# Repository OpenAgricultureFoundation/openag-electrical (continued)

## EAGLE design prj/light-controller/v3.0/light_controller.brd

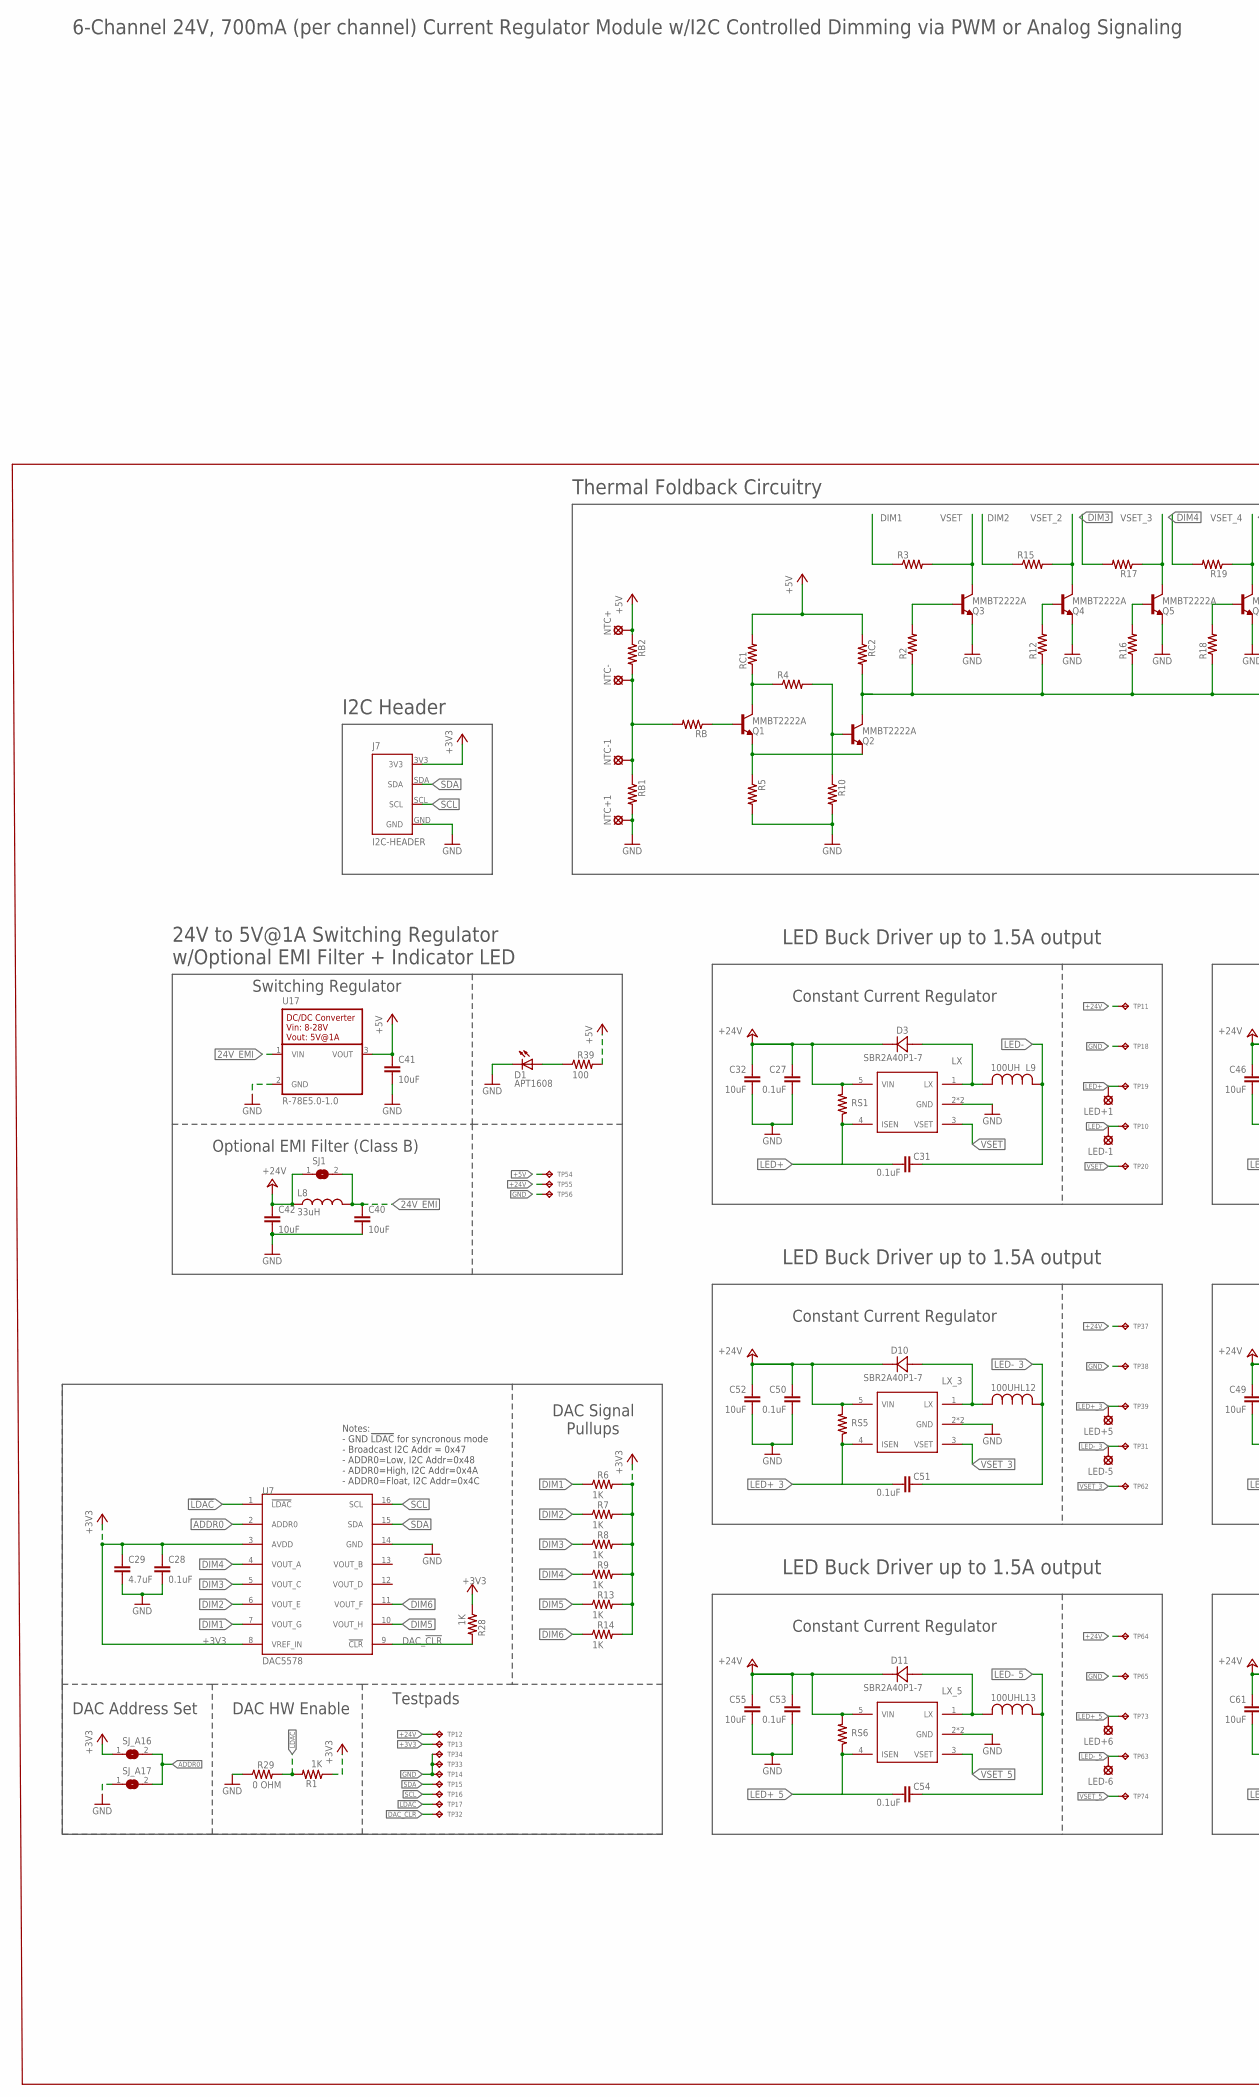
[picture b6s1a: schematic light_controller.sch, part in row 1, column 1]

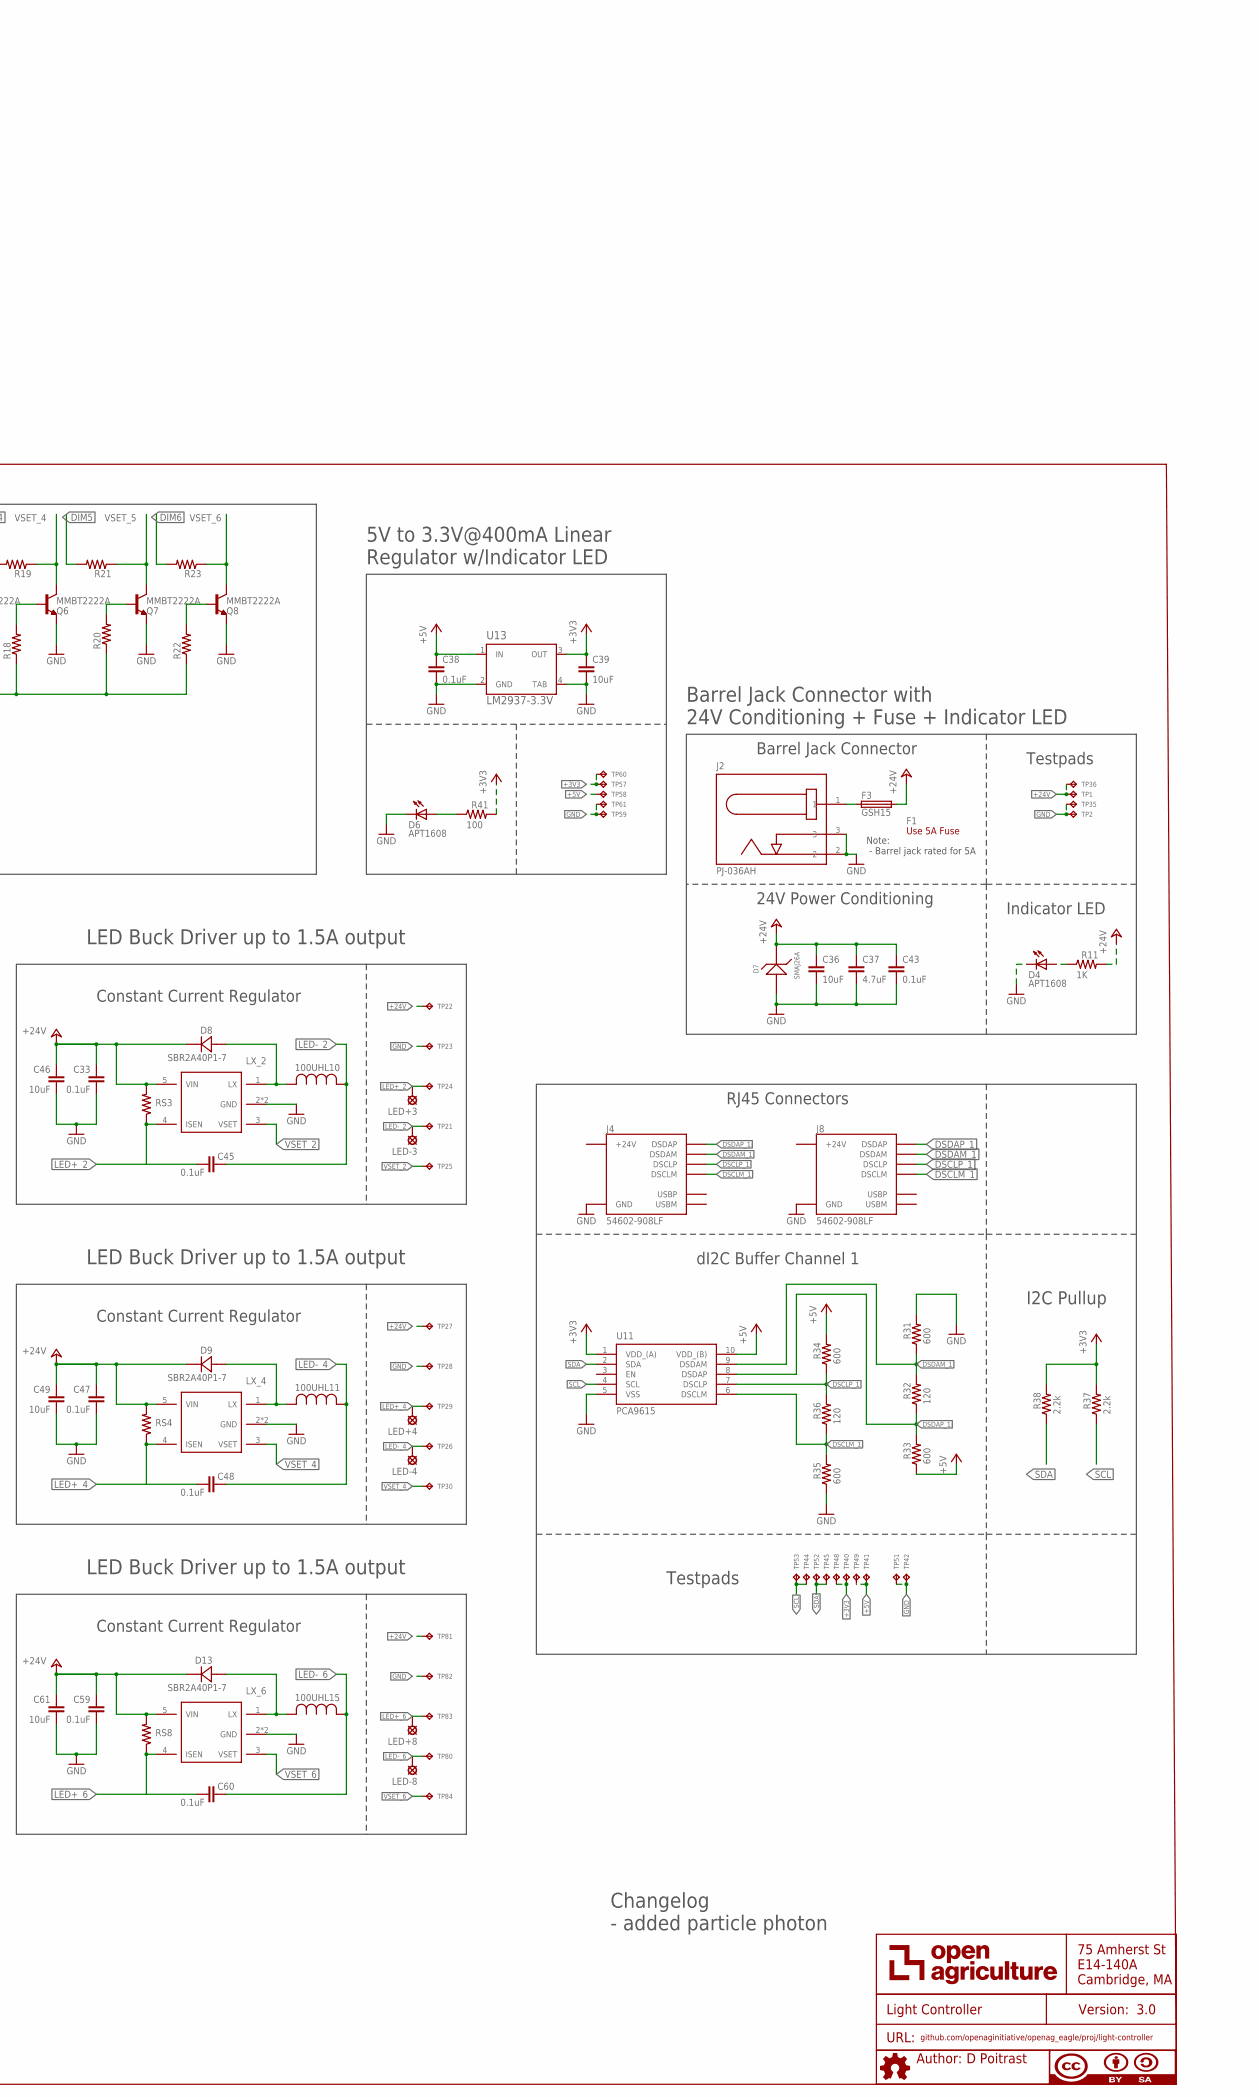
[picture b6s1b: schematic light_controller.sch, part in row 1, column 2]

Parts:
C27, C28, C31, C33, C38, C43, C45, C47, C48, C50, C51, C53, C54, C59, C60: 0.1uF; C0603
C29, C37: 4.7uF; C0805
C32, C36, C39, C40, C41, C42, C46, C49, C52, C55, C61: 10uF; C0805
D1, D4, D6: APT1608; CHIPLED_0603
D3, D8, D9, D10, D11, D13: SBR2A40P1-7; POWERDI123
D7: SMAJ26A; SMA
F1: Use 5A Fuse; FUSE-CARTRIDGE
F3: GSH15
J2: PJ-036AH; BARREL-JACK-PJ-036AH
J4, J8: 54602-908LF; RJ45-DI2C-USB-54602-908LF
J7: I2C-HEADER; HEADER-I2C
L8: 33uH; 29333C
L9, L10, L11, L12, L13, L15: 100UH; IND_BOURNS_SDR1307
LED+1, LED+3, LED+4, LED+5, LED+6, LED+8: SE14
LED-1, LED-3, LED-4, LED-5, LED-6, LED-8: SE14
NTC+, NTC+1: SE14
NTC-, NTC-1: SE14
Q1, Q2, Q3, Q4, Q5, Q6, Q7, Q8: MMBT2222A; SOT23-BEC
R1, R6, R7, R8, R9, R11, R13, R14, R28: 1K; RC0603N
R2, R3, R4, R5, R10, R12, R15, R16, R17, R18, R19, R20, R21, R22, R23: R-US_R0805W; R0805W
R29: 0 OHM; RC0603N
R31, R33, R34, R35: 600; RC0603N
R32, R36: 120; RC0603N
R37, R38: 2.2k; RC0603N
R39, R41: 100; RC0603N
RB, RB1, RB2: R-US_R0805W; R0805W
RC1, RC2: R-US_R0805W; R0805W
RS1, RS3, RS4, RS5, RS6, RS8: 6.34 ohm; R0805
SJ1: EMI-BYPASS
SJ_A16, SJ_A17: SOLDERJUMPERREFLOW_NOPASTE; SJ1
TP1, TP2, TP12, TP13, TP14, TP15, TP16, TP17, TP32, TP33, TP34, TP35, TP36, TP40, TP41, TP42, TP44, TP45, TP48, TP49, TP51, TP52, TP53, TP57, TP58, TP59, TP60, TP61: TPTP04R; TP04R
TP10, TP11, TP18, TP19, TP20, TP21, TP22, TP23, TP24, TP25, TP26, TP27, TP28, TP29, TP30, TP31, TP37, TP38, TP39, TP54, TP55, TP56, TP62, TP63, TP64, TP65, TP73, TP74, TP80, TP81, TP82, TP83, TP84: TPTP06R; TP06R
U7: DAC5578; TSSOP16
U11: PCA9615; SOP50P490X110-10N
U13: LM2937-3.3V; MP04A
U17: R-78E5.0-1.0
U$6: AUTHOR
U$7: TITLE
U$11, U$12, U$13, U$14, U$15, U$17: AL8861

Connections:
24V_EMI: C40.1, L8.2, SJ1.2, U17.1 (VIN)
24V_IN: F3.1, J2.1
!LDAC!: R1.2, R29.2, TP17.1, U7.1 (!LDAC!)
+3V3: C28.1, C29.1, C39.1, J7.3V3, R1.1, R6.2, R7.2, R8.2, R9.2, R13.2, R14.2, R28.1, R37.2, R38.2, R41.2, SJ_A16.1, TP13.1, TP40.1, TP48.1, TP57.1, TP60.1, U7.3 (AVDD), U7.8 (VREF_IN), U11.1 (VDD_(A)), U13.3 (OUT)
+5V: C38.1, C41.1, NTC+.MP, R33.1, R34.2, R39.2, RB2.1, RC1.2, RC2.1, TP41.1, TP49.1, TP54.TP, TP58.1, U11.10 (VDD_(B)), U13.1 (IN), U17.3 (VOUT)
+24V: C27.1, C32.1, C33.1, C36.1, C37.1, C42.1, C43.1, C46.1, C47.1, C49.1, C50.1, C52.1, C53.1, C55.1, C59.1, C61.1, D3.-, D7.1, D8.-, D9.-, D10.-, D11.-, D13.-, F3.2, L8.1, R11.2, RS1.2, RS3.2, RS4.2, RS5.2, RS6.2, RS8.2, SJ1.1, TP1.1, TP11.TP, TP12.1, TP22.TP, TP27.TP, TP36.1, TP37.TP, TP55.TP, TP64.TP, TP81.TP, U$11.5 (VIN), U$12.5 (VIN), U$13.5 (VIN), U$14.5 (VIN), U$15.5 (VIN), U$17.5 (VIN)
ADDR0: SJ_A16.2, SJ_A17.2, U7.2 (ADDR0)
DAC_!CLR!: R28.2, TP32.1, U7.9 (!CLR!)
DIM1: R3.1, R6.1, U7.7 (VOUT_G)
DIM2: R7.1, R15.1, U7.6 (VOUT_E)
DIM3: R8.1, R17.2, U7.5 (VOUT_C)
DIM4: R9.1, R19.2, U7.4 (VOUT_A)
DIM5: R13.1, R21.2, U7.10 (VOUT_H)
DIM6: R14.1, R23.2, U7.11 (VOUT_F)
DSCLM_1: J4.DSCLM(5) (DSCLM), J8.DSCLM(5) (DSCLM), R35.2, R36.1, U11.6 (DSCLM)
DSCLP_1: J4.DSCLP(4) (DSCLP), J8.DSCLP(4) (DSCLP), R34.1, R36.2, U11.7 (DSCLP)
DSDAM_1: J4.DSDAM(2) (DSDAM), J8.DSDAM(2) (DSDAM), R31.1, R32.2, U11.9 (DSDAM)
DSDAP_1: J4.DSDAP(1) (DSDAP), J8.DSDAP(1) (DSDAP), R32.1, R33.2, U11.8 (DSDAP)
GND: C27.2, C28.2, C29.2, C32.2, C33.2, C36.2, C37.2, C38.2, C39.2, C40.2, C41.2, C42.2, C43.2, C46.2, C47.2, C49.2, C50.2, C52.2, C53.2, C55.2, C59.2, C61.2, D1.C, D4.C, D6.C, D7.2, J2.2, J2.3, J4.GND(3) (GND), J7.GND, J8.GND(3) (GND), NTC+1.MP, Q3.E, Q4.E, Q5.E, Q6.E, Q7.E, Q8.E, R5.2, R10.2, R29.1, R31.2, R35.1, RB1.2, SJ_A17.1, TP2.1, TP14.1, TP18.TP, TP23.TP, TP28.TP, TP33.1, TP34.1, TP35.1, TP38.TP, TP42.1, TP51.1, TP56.TP, TP59.1, TP61.1, TP65.TP, TP82.TP, U7.14 (GND), U11.5 (VSS), U13.2 (GND), U13.4 (TAB), U17.2 (GND), U$11.2 (GND), U$11.44 (GND), U$12.2 (GND), U$12.44 (GND), U$13.2 (GND), U$13.44 (GND), U$14.2 (GND), U$14.44 (GND), U$15.2 (GND), U$15.44 (GND), U$17.2 (GND), U$17.44 (GND)
LED+: C31.2, LED+1.MP, RS1.1, TP19.TP, U$11.4 (ISEN)
LED+_2: C45.2, LED+3.MP, RS3.1, TP24.TP, U$12.4 (ISEN)
LED+_3: C51.2, LED+5.MP, RS5.1, TP39.TP, U$14.4 (ISEN)
LED+_4: C48.2, LED+4.MP, RS4.1, TP29.TP, U$13.4 (ISEN)
LED+_5: C54.2, LED+6.MP, RS6.1, TP73.TP, U$15.4 (ISEN)
LED+_6: C60.2, LED+8.MP, RS8.1, TP83.TP, U$17.4 (ISEN)
LED-: C31.1, L9.2, LED-1.MP, TP10.TP
LED-_2: C45.1, L10.2, LED-3.MP, TP21.TP
LED-_3: C51.1, L12.2, LED-5.MP, TP31.TP
LED-_4: C48.1, L11.2, LED-4.MP, TP26.TP
LED-_5: C54.1, L13.2, LED-6.MP, TP63.TP
LED-_6: C60.1, L15.2, LED-8.MP, TP80.TP
LX: D3.+, L9.1, U$11.1 (LX)
LX_2: D8.+, L10.1, U$12.1 (LX)
LX_3: D10.+, L12.1, U$14.1 (LX)
LX_4: D9.+, L11.1, U$13.1 (LX)
LX_5: D11.+, L13.1, U$15.1 (LX)
LX_6: D13.+, L15.1, U$17.1 (LX)
unnamed: D1.A, R39.1
unnamed: D6.A, R41.1
unnamed: D4.A, R11.1
unnamed: Q1.B, RB.1
unnamed: Q1.C, R4.1, RC1.1
unnamed: Q1.E, Q2.E, R5.1
unnamed: Q3.B, R2.2
unnamed: Q2.B, R4.2, R10.1
unnamed: Q4.B, R12.2
unnamed: Q2.C, R2.1, R12.1, R16.1, R18.1, R20.1, R22.1, RC2.2
unnamed: Q5.B, R16.2
unnamed: Q6.B, R18.2
unnamed: Q7.B, R20.2
unnamed: Q8.B, R22.2
unnamed: NTC-.MP, NTC-1.MP, RB.2, RB1.1, RB2.2
SCL: J7.SCL, R37.1, TP16.1, TP44.1, TP53.1, U7.16 (SCL), U11.4 (SCL)
SDA: J7.SDA, R38.1, TP15.1, TP45.1, TP52.1, U7.15 (SDA), U11.2 (SDA)
VSET: Q3.C, R3.2, TP20.TP, U$11.3 (VSET)
VSET_2: Q4.C, R15.2, TP25.TP, U$12.3 (VSET)
VSET_3: Q5.C, R17.1, TP62.TP, U$14.3 (VSET)
VSET_4: Q6.C, R19.1, TP30.TP, U$13.3 (VSET)
VSET_5: Q7.C, R21.1, TP74.TP, U$15.3 (VSET)
VSET_6: Q8.C, R23.1, TP84.TP, U$17.3 (VSET)

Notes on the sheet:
Notes: - GND !LDAC! for syncronous mode - Broadcast I2C Addr = 0x47 - ADDR0=Low, I2C Addr=0x48 - ADDR0=High, I2C Addr=0x4A - ADDR0=Float, I2C Addr=0x4C
I2C Header
6-Channel 24V, 700mA (per channel) Current Regulator Module w/I2C Controlled Dimming via PWM or Analog Signaling
Changelog - added particle photon
5V to 3.3V@400mA Linear Regulator w/Indicator LED
dI2C Buffer Channel 1
RJ45 Connectors
24V to 5V@1A Switching Regulator w/Optional EMI Filter + Indicator LED
Switching Regulator
Optional EMI Filter (Class B)
Testpads
I2C Pullup
Barrel Jack Connector
Barrel Jack Connector with 24V Conditioning + Fuse + Indicator LED
24V Power Conditioning
Indicator LED
DAC Signal Pullups
DAC Address Set
DAC HW Enable
Note: - Barrel jack rated for 5A
LED Buck Driver up to 1.5A output
Constant Current Regulator
Thermal Foldback Circuitry

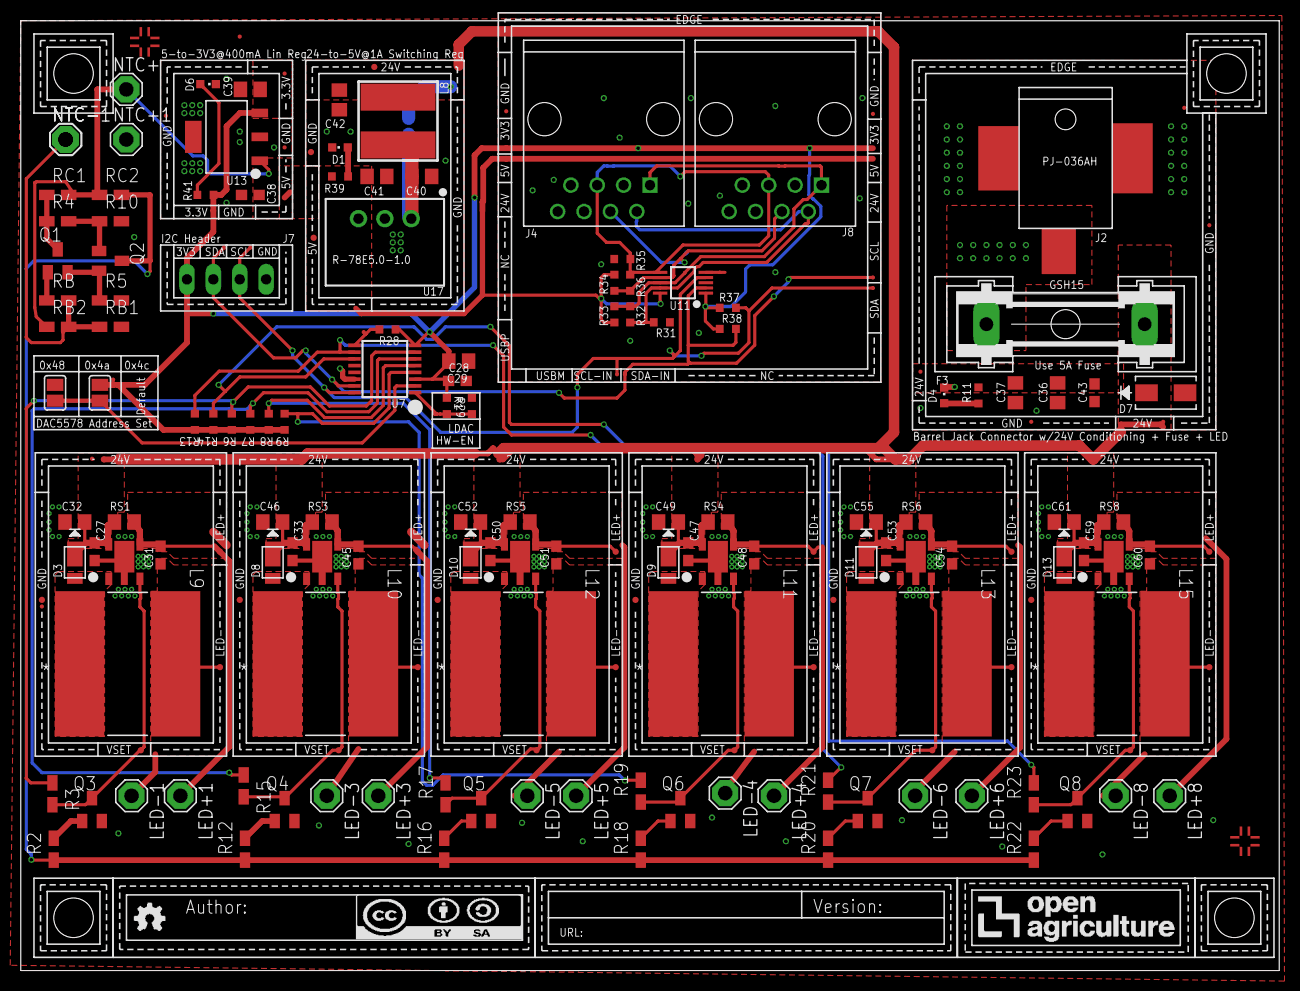
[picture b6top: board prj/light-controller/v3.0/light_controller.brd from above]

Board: 2 copper layers, 121.1 x 91.4 mm, 204 parts (1 on the bottom side), 60 nets.

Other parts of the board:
U$1, U$2, U$3, U$4: CORNER
U$8: LOGO
U$10, U$16: PASSER
